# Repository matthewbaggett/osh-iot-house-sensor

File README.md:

# osh-iot-house-sensor
An OpenSourceHardware IoT House sensor, featuring wifi connectivity, temperature, light, humidity and presence detection

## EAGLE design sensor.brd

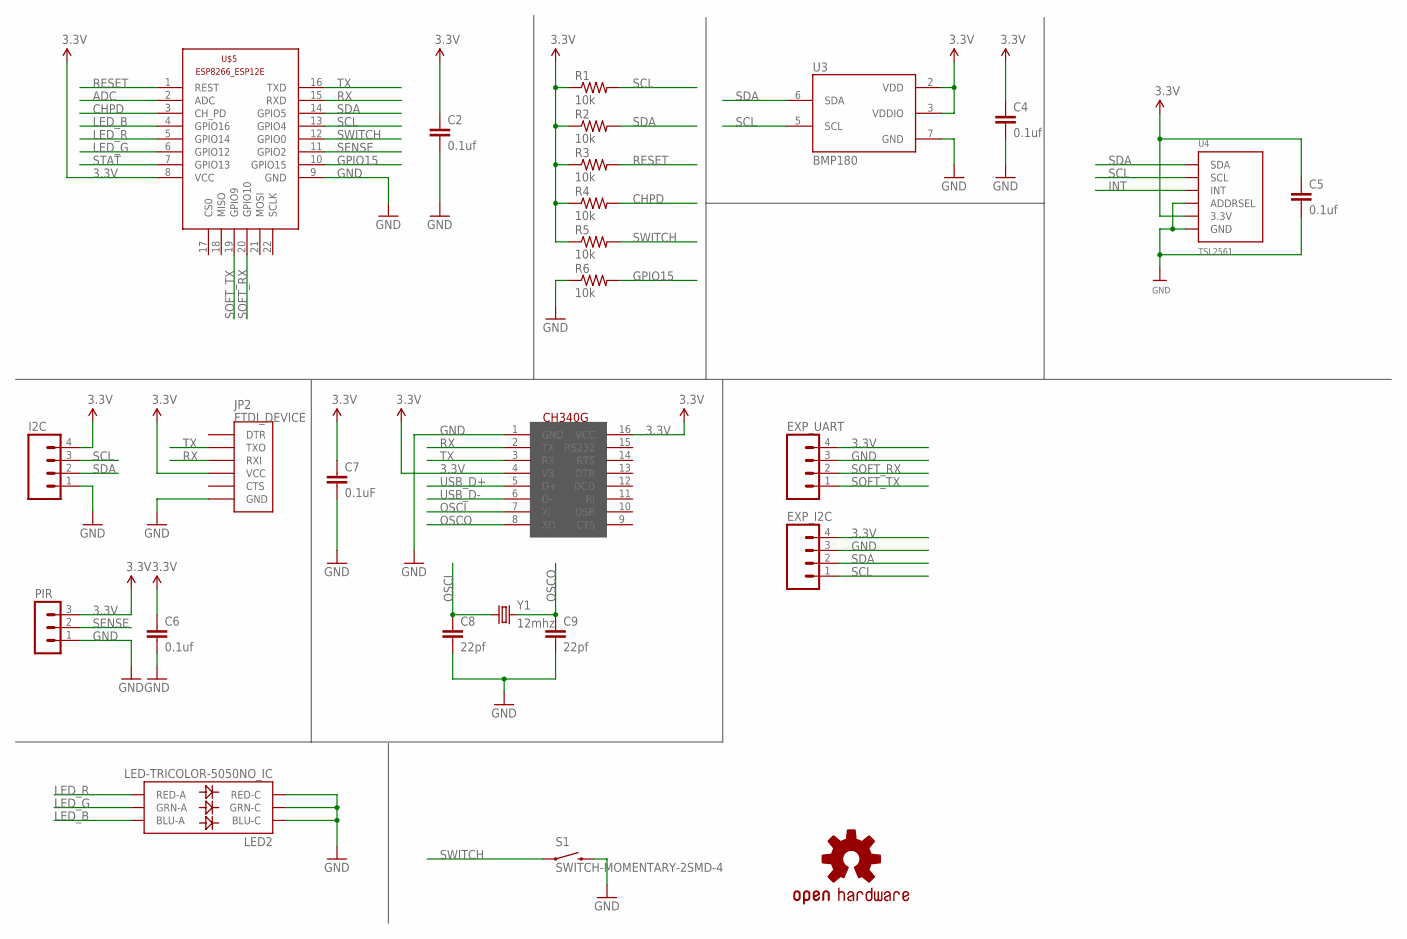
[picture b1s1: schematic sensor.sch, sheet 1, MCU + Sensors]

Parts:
C2, C4, C5, C6: 0.1uf; 0805
C7: 0.1uF; C0805
C8, C9: 22pf; C0805
EXP_I2C: M04LOCK; 1X04_LOCK
EXP_UART: M04LOCK; 1X04_LOCK
I2C: M04JST-PTH; JST-4-PTH
JP2: FTDI_DEVICE; FTDI_DEVICE_SIDE
LED2: LED-TRICOLOR-5050NO_IC; LED-TRICOLOR-5050
LOGO1: OSHW-LOGOL; OSHW-LOGO-L
PIR: MA03-1
R1, R2, R3, R4, R5, R6: 10k; 0805
S1: SWITCH-MOMENTARY-2SMD-4; TACTILE_SWITCH_TALL
U3: BMP180
U4: TSL2561; TSL2561_FN
U$5: ESP8266-12EESP8266-ESP12E; ESP8266-ESP12E
U$11: CH340G; SOIC16
Y1: 12mhz; HC49UP

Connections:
3.3V: C2.1, C4.1, C5.1, C6.1, C7.1, EXP_I2C.4, EXP_UART.4, I2C.4, JP2.P$4 (VCC), PIR.3, R1.1, R2.1, R3.1, R4.1, R5.1, U3.2 (VDD), U3.3 (VDDIO), U4.VDD (3.3V), U$5.8 (VCC), U$11.4 (V3), U$11.16 (VCC); also elsewhere on the board
ADC: U$5.2 (ADC)
CHPD: R4.2, U$5.3 (CH_PD)
GND: C2.2, C4.2, C5.2, C6.2, C7.2, C8.2, C9.2, EXP_I2C.3, EXP_UART.3, I2C.1, JP2.P$6 (GND), LED2.4 (BLU-C), LED2.5 (RED-C), LED2.6 (GRN-C), PIR.1, R6.1, S1.B2 (2), U3.7 (GND), U4.ADR (ADDRSEL), U4.VSS (GND), U$5.9 (GND), U$11.1 (GND); also elsewhere on the board
GPIO15: R6.2, U$5.10 (GPIO15)
INT: U4.INT
LED_B: LED2.3 (BLU-A), U$5.4 (GPIO16)
LED_G: LED2.1 (GRN-A), U$5.6 (GPIO12)
LED_R: LED2.2 (RED-A), U$5.5 (GPIO14)
OSCI: C8.1, U$11.7 (XI), Y1.1
OSCO: C9.1, U$11.8 (XO), Y1.2
RESET: R3.2, U$5.1 (REST)
RX: JP2.P$3 (RXI), U$5.15 (RXD), U$11.2 (TX)
SCL: EXP_I2C.1, I2C.3, R1.2, U3.5 (SCL), U4.CLK (SCL), U$5.13 (GPIO4)
SDA: EXP_I2C.2, I2C.2, R2.2, U3.6 (SDA), U4.DATA (SDA), U$5.14 (GPIO5)
SENSE: PIR.2, U$5.11 (GPIO2)
SOFT_RX: EXP_UART.2, U$5.20 (GPIO10)
SOFT_TX: EXP_UART.1, U$5.19 (GPIO9)
STAT: U$5.7 (GPIO13); also elsewhere on the board
SWITCH: R5.2, S1.A2 (1), U$5.12 (GPIO0)
TX: JP2.P$2 (TXO), U$5.16 (TXD), U$11.3 (RX)
USB_D+: U$11.5 (D+); also elsewhere on the board
USB_D-: U$11.6 (D-); also elsewhere on the board

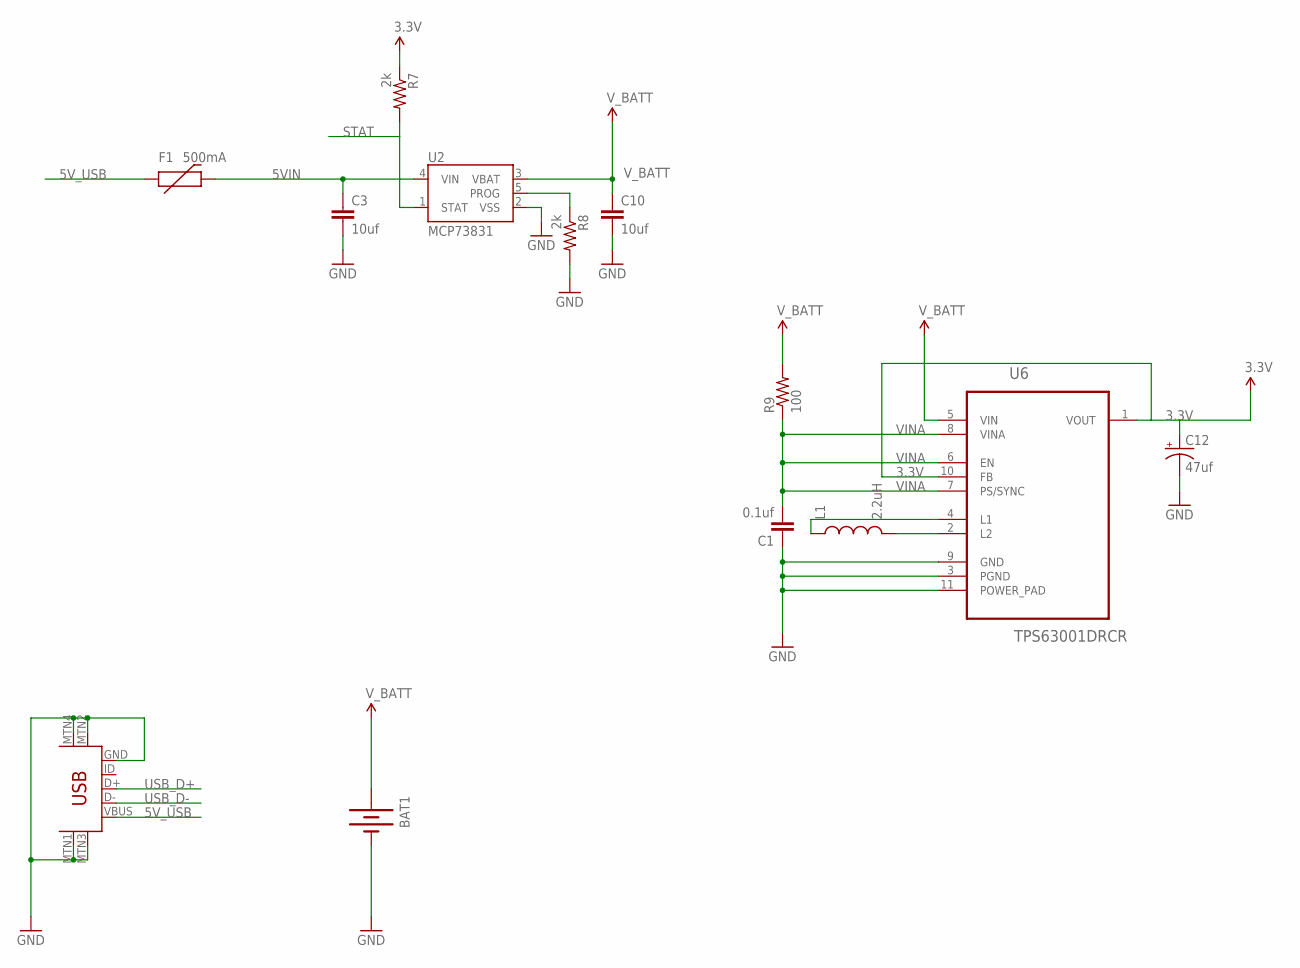
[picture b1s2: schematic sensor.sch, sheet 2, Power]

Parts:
BAT1: BATTERY18650; BATTERY_18650-HOLDER
C1: 0.1uf; 0805
C3, C10: 10uf; 0805
C12: 47uf; PANASONIC_C
F1: 500mA; PTC-1206
L1: 2.2uH; SRU5028
R7, R8: 2k; 0805
R9: 100; 0805
U2: MCP73831; SOT23-5
U6: TPS63001DRCR; SON50P300X300X100-11N
U$6: USB-MINIB-5PIN; USB-MINIB

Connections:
3.3V: C12.+, R7.1, U6.1 (VOUT), U6.10 (FB); also elsewhere on the board
5VIN: C3.1, F1.2, U2.4 (VIN)
5V_USB: F1.1, U$6.VBUS
GND: BAT1.GND@1 (-), C1.1, C3.2, C10.2, C12.-, R8.2, U2.2 (VSS), U6.3 (PGND), U6.9 (GND), U6.11 (POWER_PAD), U$6.GND, U$6.MTN1 (MTN2), U$6.MTN2 (MTN3), U$6.MTN3 (MTN1), U$6.MTN4; also elsewhere on the board
unnamed: L1.2, U6.2 (L2)
unnamed: L1.1, U6.4 (L1)
unnamed: R8.1, U2.5 (PROG)
STAT: R7.2, U2.1 (STAT); also elsewhere on the board
USB_D+: U$6.D+; also elsewhere on the board
USB_D-: U$6.D-; also elsewhere on the board
VINA: C1.2, R9.1, U6.6 (EN), U6.7 (PS/SYNC), U6.8 (VINA)
V_BATT: BAT1.PWR@1 (+), C10.1, R9.2, U2.3 (VBAT), U6.5 (VIN)

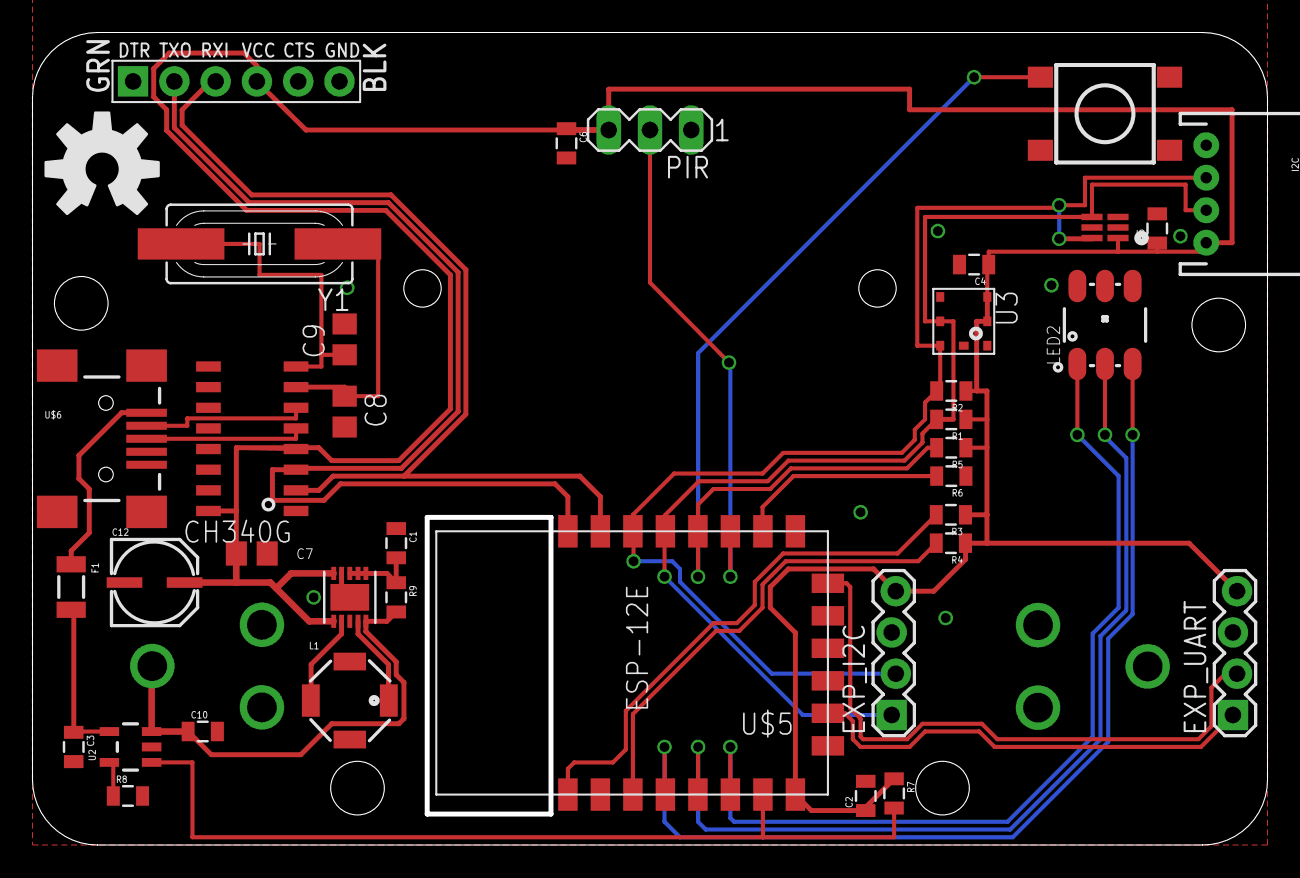
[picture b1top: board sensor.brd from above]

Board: 2 copper layers, 75.7 x 49.7 mm, 39 parts (1 on the bottom side), 28 nets.

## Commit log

2016-11-01 Added some drill holes for mounting the PCB into a housing.
2016-11-17 lipo 18650 cell, TP4056 1A boost/charge controller
2016-11-17 Move schematic around to be more pleasing, add i2c header as per @badspyro's request.
2016-11-18 Redo.. but oops.
2016-11-18 Redone this time without the esp8266's housing clipping through the PIR variable resistors
2016-12-04 Moving to using MCP7381 and TPS63001.. Damn tiny ass packages.
2016-12-04 Fix airwire
2016-12-04 Tart the PCB up a bit, nice 45 degree bends. Add a 0.1uf cap across the PIR sensor.

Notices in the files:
parts and their libraries:
SparkFun-Capacitors: Licensing: Creative Commons ShareAlike 4.0 International - https://creativecommons.org/licenses/by-sa/4.0
SparkFun: Licensing: CC v3.0 Share-Alike You are welcome to use this library for commercial purposes.
